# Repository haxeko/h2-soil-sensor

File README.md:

# H2 Soil Sensor — cảm biến độ ẩm đất Matter over Thread chạy pin

**Phiên bản 3:** bo mạch gọn **26 × 45 mm** chỉ gồm **ESP32-H2-WROOM-02C** + **tầng nguồn pin** (1 × CR123A, buck-boost
**TPS63900**, Iq 75 nA) + **một cổng J4 JST-PH 2.0 3P** cho module phổ biến **“Capacitive Soil Moisture Sensor v1.2”**
(module điện dung, ngõ ra analog AOUT). Pin hàn vào **2 pad J3** (“+” vuông, “−” tròn) bằng dây của hộp pin; nạp firmware qua
**8 pad tròn J1** (kẹp pogo 2.54 mm hoặc hàn dây) thay cho header. Thiết bị kết nối **Matter over Thread** như
**Sleepy End Device / ICD**; module chỉ được cấp nguồn (rail VSENS qua MOSFET) trong ~1.5 s mỗi lần đo.

| | |
|---|---|
|  | **Phần cứng**: KiCad (schematic phân cấp 5 sheet + PCB 2 lớp 26 × 45 mm, đã đi dây, DRC sạch), Gerber/BOM/CPL cho JLCPCB; linh kiện trên bo ≈ 2.1 USD (không gồm module ESP).<br><br>**Firmware**: ESP-IDF v6.0.2 + esp-matter (Matter 1.5): Soil Sensor (Soil Measurement), Humidity Sensor (bản sao độ ẩm đất, tương thích Apple/Google), Power Source (pin), ICD SIT/LIT, light-sleep, hiệu chuẩn bằng nút nhấn.<br><br>**Tuổi thọ pin ước tính** (đo mỗi 15 phút): ~2.2 năm (SIT, poll 15 s) – ~2.9 năm (LIT, poll 60 s); ~3.3 năm với LIT + đo mỗi 30 phút. |

## Tài liệu (tiếng Việt)

1. [Sơ đồ khối, lựa chọn linh kiện và module cảm biến](docs/01-so-do-khoi-va-linh-kien.md)
2. [Schematic chi tiết theo khối (nguồn, MCU, cổng cảm biến, nút/LED/pad nạp)](docs/02-schematic.md) — PDF: [`hardware/docs/schematic.pdf`](hardware/docs/schematic.pdf)
3. [BOM kèm mã LCSC (không gồm module ESP) và vật tư ngoài BOM](docs/03-bom.md)
4. [Hướng dẫn layout PCB](docs/04-layout-pcb.md)
5. [Dòng tiêu thụ từng trạng thái và tuổi thọ pin](docs/05-nang-luong-va-tuoi-tho-pin.md) — mô hình: [`docs/power_budget.py`](docs/power_budget.py)
6. [Cấu trúc project firmware và code chính](docs/06-firmware.md)
7. [Rủi ro và lưu ý khi dùng ngoài trời](docs/07-rui-ro-ngoai-troi.md)

## Cấu trúc repository

```
hardware/
├── h2-soil-sensor.kicad_pro / .kicad_sch / .kicad_pcb   # project KiCad (mở bằng KiCad ≥ 7)
├── power.kicad_sch, mcu.kicad_sch, sensors.kicad_sch, ui.kicad_sch
├── lib/h2soil.kicad_sym, lib/h2soil.pretty/             # symbol/footprint riêng (module ESP32-H2, pad nạp 2×4, WSON-10 via 0.3 mm)
├── fab/                                                 # Gerber+khoan (zip), BOM & CPL JLCPCB, danh sách không lắp máy
├── docs/                                                # schematic.pdf, pcb_top/bottom, assembly_top.pdf, render*.png, drc_report.txt
└── tools/                                               # script sinh schematic/PCB/fab từ design.py (+ router A*)
firmware/                                                # project ESP-IDF + esp-matter
docs/                                                    # tài liệu thiết kế
```

## Trạng thái kiểm chứng

| Hạng mục | Kết quả |
|---|---|
| Schematic | Netlist xuất bằng `kicad-cli` khớp 100 % với `design.py` (41 net, 43 ký hiệu = 39 linh kiện + 4 PWR_FLAG, mọi chân); PWR_FLAG đủ |
| PCB | 27/27 net tín hiệu đã đi dây (GND bằng đổ đồng 2 lớp); **DRC KiCad: 0 vi phạm, 0 pad chưa nối, 0 lỗi footprint** |
| Linh kiện | Mã LCSC kiểm tra tồn kho/giá qua API JLCPCB (11/2026) |
| Firmware | `idf.py build` thành công (ESP-IDF v6.0.2, esp-matter main / Matter 1.5, esp32h2), 1.66 MB, còn 16 % phân vùng OTA, không cảnh báo trong mã ứng dụng |
| Chưa làm được trong môi trường này | Chạy thử trên phần cứng thật, đo dòng thực tế, thử và hiệu chuẩn với module thật, kiểm tra anten/vỏ — cần bo mẫu |

## Bắt đầu nhanh

```bash
# Phần cứng: mở hardware/h2-soil-sensor.kicad_pro trong KiCad; file sản xuất ở hardware/fab/
# Firmware:
. esp-idf/export.sh && . esp-matter/export.sh
cd firmware && idf.py set-target esp32h2 && idf.py build
idf.py -p /dev/ttyACM0 flash monitor     # USB Serial/JTAG qua pad J1 (D+ = 8, D− = 7, GND = 2), pin đã lắp
```

1. Cáp đi kèm module thường là PH2.0 → đầu Dupont cái, **không cắm được vào J4**: dùng cáp PH2.0-3P hai đầu (nối thẳng) hoặc
   bấm lại đầu; đo để chắc GND → J4-1, VCC → J4-2, AOUT → J4-3.
2. Sau khi nạp: thiết bị mở BLE commissioning 15 phút — quét mã QR in trong log bằng ứng dụng Home (Apple Home, Google Home,
   SmartThings, Home Assistant…).
3. Hiệu chuẩn module: nhấn 2 lần nút khi đầu dò khô trong không khí (KHÔ), 3 lần khi đầu dò ngập nước tới vạch giới hạn (ƯỚT).

## Các phiên bản

| Phiên bản | Commit | Mô tả |
|---|---|---|
| v1 | `3c3f9e9` | Bo dạng que cắm đất 26 × 212 mm: đầu dò điện dung in trên PCB + TLC555, SHT40 và NTC trên bo, đế pin CR123A trên bo |
| v2 | `08ab9fe` | Bo 36 × 60 mm cắm module có sẵn: module đất, module I²C nhiệt/ẩm, đầu dò NTC; pin qua JST hoặc pad |
| v3 | hiện tại | Bo 26 × 45 mm chỉ cho module “Capacitive Soil Moisture Sensor v1.2”; pad nạp tròn thay header |

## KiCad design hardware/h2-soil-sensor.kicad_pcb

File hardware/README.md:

# Hardware (KiCad) – bo mạch v3, 26 × 45 mm

- Mở `h2-soil-sensor.kicad_pro` bằng KiCad 7/8/9. Thư viện riêng `h2soil` (symbol ESP32-H2-WROOM-02C, VBAT, VSENS; footprint
  module ESP32-H2, pad nạp `ProgPads_2x04_P2.54mm_D1.5mm` và WSON-10 via nhiệt 0.3 mm) đã khai báo trong `sym-lib-table` /
  `fp-lib-table` của project (`${KIPRJMOD}/lib/...`).
- `docs/schematic.pdf` – schematic 5 trang (sơ đồ khối, Power, MCU, Sensors, UI); `docs/pcb_top.*`, `docs/pcb_bottom.*`
  (mặt dưới nhìn gương), `docs/assembly_top.pdf` (vị trí + ký hiệu linh kiện); `docs/render.png`, `render_top.png`,
  `render_bottom.png` (ảnh minh hoạ); `docs/drc_report.txt` – báo cáo DRC (0 vi phạm, 0 pad chưa nối).
- `fab/h2-soil-sensor_gerbers.zip` (Gerber + khoan Excellon), `fab/h2-soil-sensor_BOM_JLCPCB.csv` và
  `fab/h2-soil-sensor_CPL_JLCPCB.csv` (35 linh kiện SMT lắp máy, kể cả U1), `fab/h2-soil-sensor_not_assembled.csv` (module ESP,
  J4 THT hàn tay, pad J1/J3).

## Cổng kết nối

| Ký hiệu | Loại | Chân |
|---|---|---|
| J3 | 2 pad xuyên lỗ hàn dây pin (lỗ 1.1 mm, bước 4.6 mm) | pad 1 vuông = “+” (VBAT_RAW), pad 2 tròn = “−” (GND); silkscreen “− BAT +” |
| J4 | JST-PH 2.0 3P (B3B-PH-K-S) – module độ ẩm đất | 1 = GND, 2 = VCC (VSENS), 3 = AOUT; J4 xoay 180°: chân 1 (GND) ở bên phải, nhãn silkscreen “A V G” |
| J1 | 8 pad tròn SMD Ø1.5 mm, lưới 2.54 mm, 2 hàng × 4, không phủ kem hàn | hàng sát mép bo (trái → phải): 1 = 3V3, 3 = TX, 5 = EN, 7 = D−; hàng trong: 2 = GND, 4 = RX, 6 = IO9, 8 = D+; pad 1 có chữ “1” |

Cáp đi kèm module thường là PH2.0 → Dupont cái, không vừa J4: dùng cáp PH2.0-3P hai đầu nối thẳng (hoặc bấm lại đầu) và đo
để chắc GND → GND trước khi cắm.

## Tái tạo từ script

Toàn bộ schematic/PCB được sinh từ `tools/design.py` (danh sách linh kiện, net, footprint, mã LCSC, ghi chú):

```bash
cd tools
python3 gen_footprints.py ..
python3 gen_schematic.py ..
python3 check_netlist.py ../h2-soil-sensor.kicad_sch    # "nets: 41  components checked: 43 ... OK"
python3 gen_pcb.py          # đặt linh kiện + đi dây (router.py) + đổ đồng + DRC; tự chạy với PYTHONHASHSEED=0 → kết quả lặp lại
python3 make_fab.py         # Gerber/khoan zip, BOM/CPL JLCPCB, not_assembled.csv, PDF, pcb_top/bottom.png
python3 render.py           # ảnh minh hoạ render_top/render_bottom/render.png
```

Yêu cầu: KiCad 7 (`kicad-cli`, module Python `pcbnew`), Python ≥ 3.10, numpy, Pillow, poppler-utils (render ảnh).
Các script giả định thư viện KiCad ở `/usr/share/kicad/{symbols,footprints}` (sửa hằng `KICAD_FP` / `KICAD_SYM_DIR` nếu khác).
Lưu ý: chạy lại `gen_pcb.py` sẽ ghi đè mọi chỉnh sửa tay trong `.kicad_pcb`.

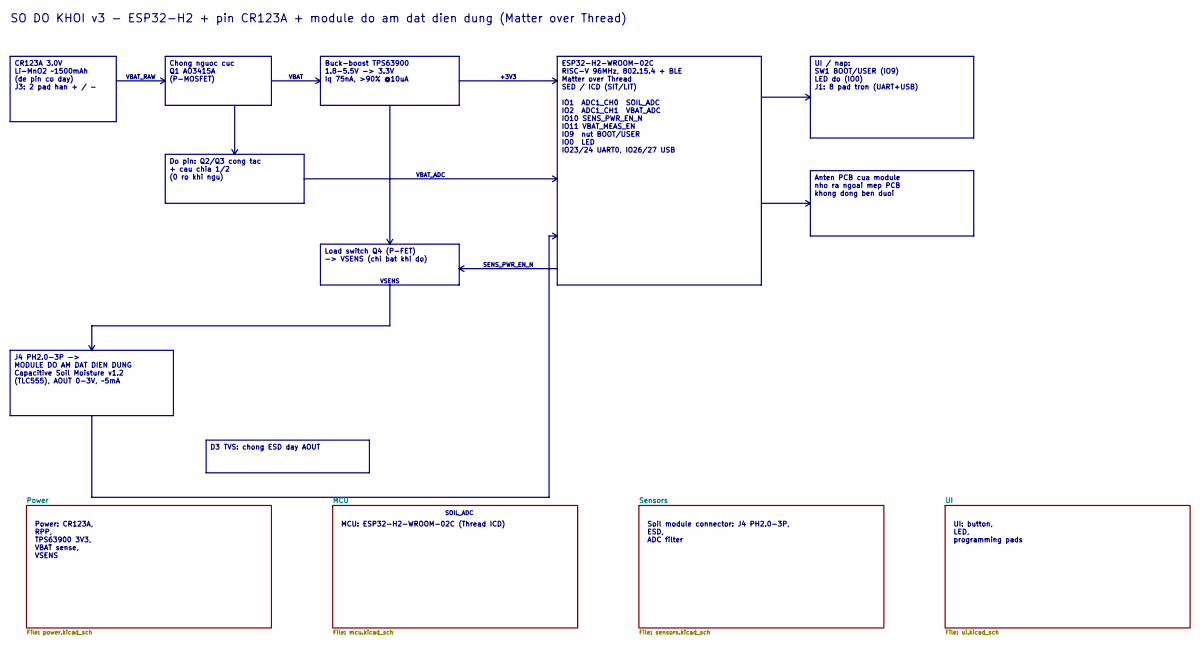
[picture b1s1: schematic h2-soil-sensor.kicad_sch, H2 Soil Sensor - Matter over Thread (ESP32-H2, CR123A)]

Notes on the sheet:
Power: CR123A, RPP, TPS63900 3V3, VBAT sense, VSENS
MCU: ESP32-H2-WROOM-02C (Thread ICD)
Soil module connector: J4 PH2.0-3P, ESD, ADC filter
UI: button, LED, programming pads
SO DO KHOI v3 - ESP32-H2 + pin CR123A + module do am dat dien dung (Matter over Thread)
CR123A 3.0V Li-MnO2 ~1500mAh (de pin co day) J3: 2 pad han + / -
Chong nguoc cuc Q1 AO3415A (P-MOSFET)
Buck-boost TPS63900 1.8-5.5V -> 3.3V Iq 75nA, >90% @10uA
ESP32-H2-WROOM-02C RISC-V 96MHz, 802.15.4 + BLE Matter over Thread SED / ICD (SIT/LIT) IO1 ADC1_CH0 SOIL_ADC IO2 ADC1_CH1 VBAT_ADC IO10 SENS_PWR_EN_N IO11 VBAT_MEAS_EN IO9 nut BOOT/USER IO0 LED IO23/24 UART0, IO26/27 USB
Do pin: Q2/Q3 cong tac + cau chia 1/2 (0 ro khi ngu)
Load switch Q4 (P-FET) -> VSENS (chi bat khi do)
J4 PH2.0-3P -> MODULE DO AM DAT DIEN DUNG Capacitive Soil Moisture v1.2 (TLC555), AOUT 0-3V, ~5mA
D3 TVS: chong ESD day AOUT
UI / nap: SW1 BOOT/USER (IO9) LED do (IO0) J1: 8 pad tron (UART+USB)
Anten PCB cua module nho ra ngoai mep PCB khong dong ben duoi
VBAT_RAW
VBAT
+3V3
VBAT_ADC
SENS_PWR_EN_N
VSENS
SOIL_ADC

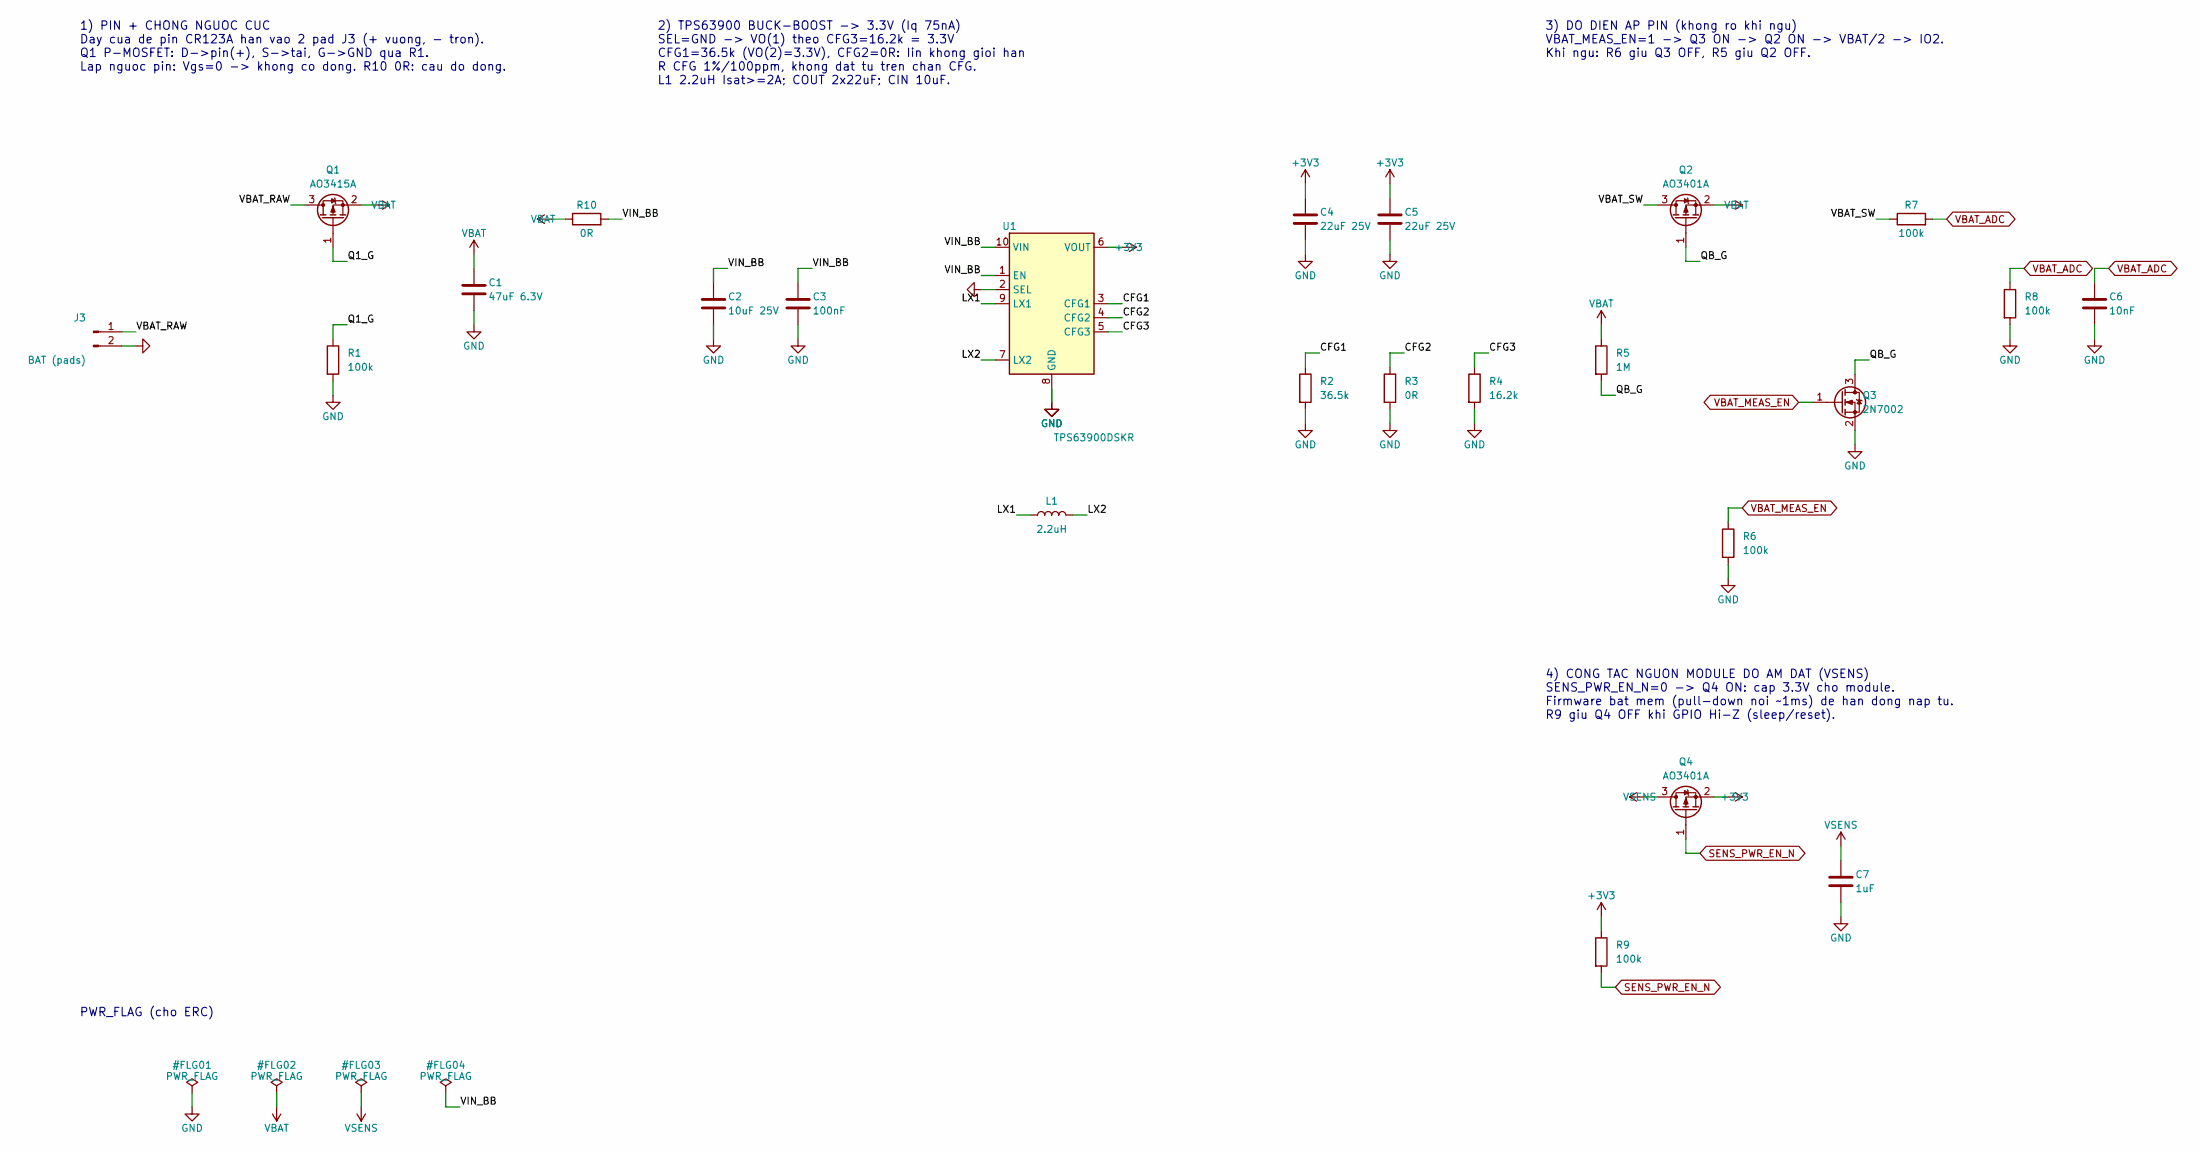
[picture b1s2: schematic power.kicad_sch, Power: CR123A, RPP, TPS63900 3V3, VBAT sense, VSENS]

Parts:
C1: 47uF 6.3V; C_0805_2012Metric; MPN CL21A476MQYNNNE; LCSC C16780
C2: 10uF 25V; C_0805_2012Metric; MPN CL21A106KAYNNNE; LCSC C15850
C3: 100nF; C_0603_1608Metric; MPN CC0603KRX7R9BB104; LCSC C14663
C4, C5: 22uF 25V; C_0805_2012Metric; MPN CL21A226MAQNNNE; LCSC C45783
C6: 10nF; C_0603_1608Metric; MPN CL10B103KB8NNNC; LCSC C1589
C7: 1uF; C_0603_1608Metric; MPN CL10A105KB8NNNC; LCSC C15849
J3: BAT (pads); SolderWire-0.5sqmm_1x02_P4.6mm_D0.9mm_OD2.1mm
L1: 2.2uH; L_1008_2520Metric; MPN TFM252012ALMA2R2MTAA; LCSC C404804
Q1: AO3415A; SOT-23; MPN AO3415A; LCSC C133233
Q2, Q4: AO3401A; SOT-23; MPN AO3401A; LCSC C15127
Q3: 2N7002; SOT-23; MPN 2N7002; LCSC C8545
R1, R6, R7, R8, R9: 100k; R_0603_1608Metric; MPN 0603WAF1003T5E; LCSC C25803
R2: 36.5k; R_0603_1608Metric; MPN 0603WAF3652T5E; LCSC C23029
R3, R10: 0R; R_0603_1608Metric; MPN 0603WAF0000T5E; LCSC C21189
R4: 16.2k; R_0603_1608Metric; MPN 0603WAF1622T5E; LCSC C22885
R5: 1M; R_0603_1608Metric; MPN 0603WAF1004T5E; LCSC C22935
U1: TPS63900DSKR; WSON-10-1EP_2.5x2.5mm_P0.5mm_EP1.2x2mm_ThermalVias_0.3mm; MPN TPS63900DSKR; LCSC C1518762

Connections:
+3V3: C4.1, C5.1, Q4.2 (S), R9.1, U1.6 (VOUT); also elsewhere on the board
CFG1: R2.1, U1.3 (CFG1)
CFG2: R3.1, U1.4 (CFG2)
CFG3: R4.1, U1.5 (CFG3)
GND: C1.2, C2.2, C3.2, C4.2, C5.2, C6.2, C7.2, J3.2, Q3.2 (S), R1.2, R2.2, R3.2, R4.2, R6.2, R8.2, U1.2 (SEL), U1.8 (GND), U1.11 (GND); also elsewhere on the board
LX1: L1.1, U1.9 (LX1)
LX2: L1.2, U1.7 (LX2)
Q1_G: Q1.1 (G), R1.1
QB_G: Q2.1 (G), Q3.3 (D), R5.2
SENS_PWR_EN_N: Q4.1 (G), R9.2; also elsewhere on the board
VBAT: C1.1, Q1.2 (S), Q2.2 (S), R5.1, R10.1
VBAT_ADC: C6.1, R7.2, R8.1; also elsewhere on the board
VBAT_MEAS_EN: Q3.1 (G), R6.1; also elsewhere on the board
VBAT_RAW: J3.1, Q1.3 (D)
VBAT_SW: Q2.3 (D), R7.1
VIN_BB: C2.1, C3.1, R10.2, U1.1 (EN), U1.10 (VIN)
VSENS: C7.1, Q4.3 (D); also elsewhere on the board

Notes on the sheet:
1) PIN + CHONG NGUOC CUC Day cua de pin CR123A han vao 2 pad J3 (+ vuong, - tron). Q1 P-MOSFET: D->pin(+), S->tai, G->GND qua R1. Lap nguoc pin: Vgs=0 -> khong co dong. R10 0R: cau do dong.
2) TPS63900 BUCK-BOOST -> 3.3V (Iq 75nA) SEL=GND -> VO(1) theo CFG3=16.2k = 3.3V CFG1=36.5k (VO(2)=3.3V), CFG2=0R: Iin khong gioi han R CFG 1%/100ppm, khong dat tu tren chan CFG. L1 2.2uH Isat>=2A; COUT 2x22uF; CIN 10uF.
3) DO DIEN AP PIN (khong ro khi ngu) VBAT_MEAS_EN=1 -> Q3 ON -> Q2 ON -> VBAT/2 -> IO2. Khi ngu: R6 giu Q3 OFF, R5 giu Q2 OFF.
4) CONG TAC NGUON MODULE DO AM DAT (VSENS) SENS_PWR_EN_N=0 -> Q4 ON: cap 3.3V cho module. Firmware bat mem (pull-down noi ~1ms) de han dong nap tu. R9 giu Q4 OFF khi GPIO Hi-Z (sleep/reset).
PWR_FLAG (cho ERC)

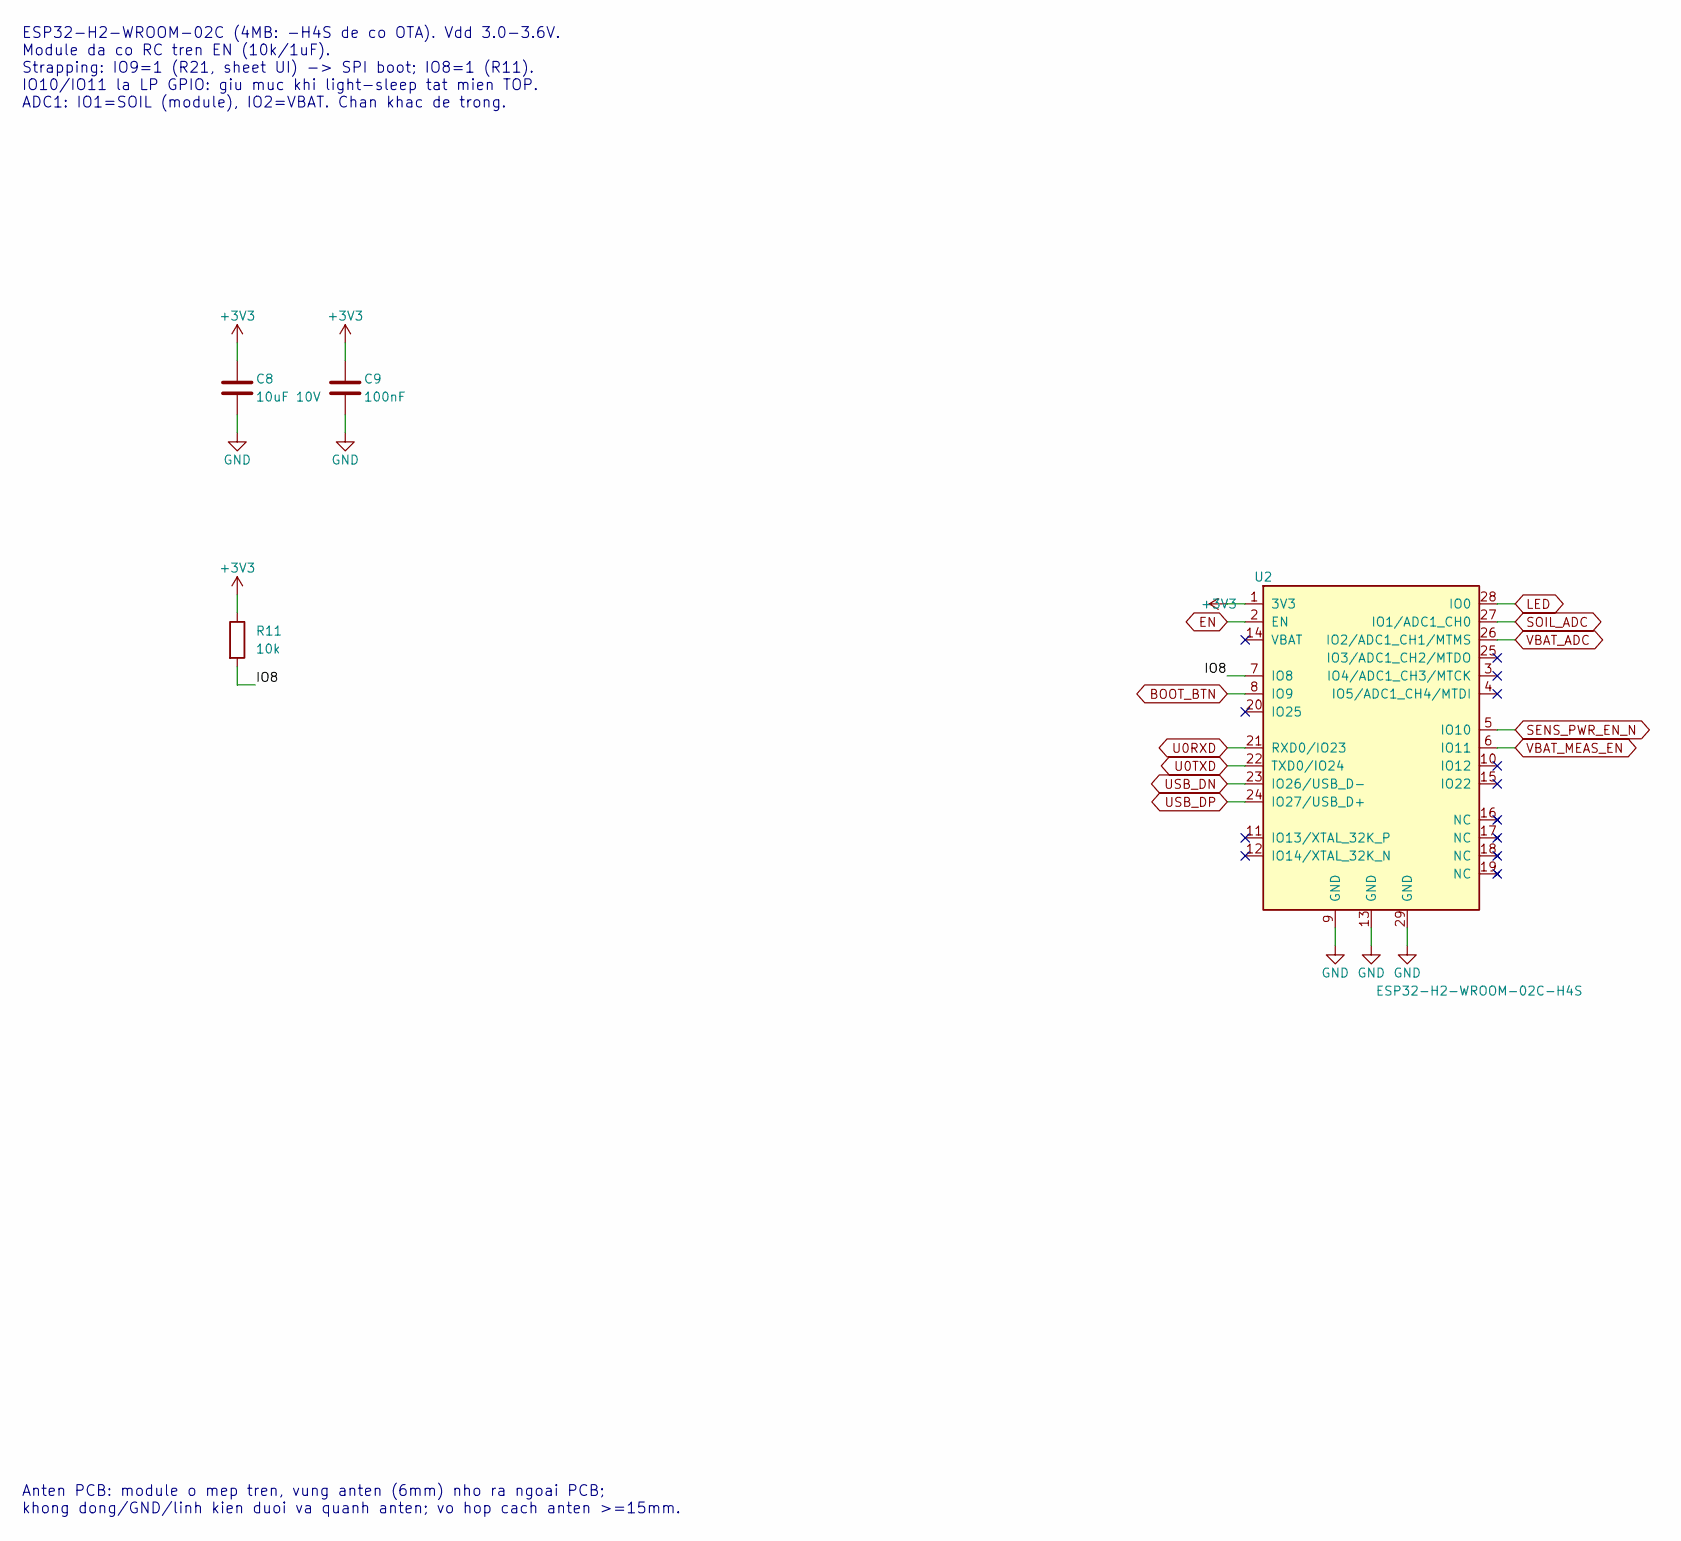
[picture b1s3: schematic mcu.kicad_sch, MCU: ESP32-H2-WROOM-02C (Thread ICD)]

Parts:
C8: 10uF 10V; C_0603_1608Metric; MPN CL10A106KP8NNNC; LCSC C19702
C9: 100nF; C_0603_1608Metric; MPN CC0603KRX7R9BB104; LCSC C14663
R11: 10k; R_0603_1608Metric; MPN 0603WAF1002T5E; LCSC C25804
U2: ESP32-H2-WROOM-02C-H4S; ESP32-H2-WROOM-02C; MPN ESP32-H2-WROOM-02C-H4S

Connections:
+3V3: C8.1, C9.1, R11.1, U2.1 (3V3); also elsewhere on the board
BOOT_BTN: U2.8 (IO9); also elsewhere on the board
EN: U2.2 (EN); also elsewhere on the board
GND: C8.2, C9.2, U2.9 (GND), U2.13 (GND), U2.29 (GND); also elsewhere on the board
IO8: R11.2, U2.7 (IO8)
LED: U2.28 (IO0); also elsewhere on the board
SENS_PWR_EN_N: U2.5 (IO10); also elsewhere on the board
SOIL_ADC: U2.27 (IO1/ADC1_CH0); also elsewhere on the board
U0RXD: U2.21 (RXD0/IO23); also elsewhere on the board
U0TXD: U2.22 (TXD0/IO24); also elsewhere on the board
USB_DN: U2.23 (IO26/USB_D-); also elsewhere on the board
USB_DP: U2.24 (IO27/USB_D+); also elsewhere on the board
VBAT_ADC: U2.26 (IO2/ADC1_CH1/MTMS); also elsewhere on the board
VBAT_MEAS_EN: U2.6 (IO11); also elsewhere on the board

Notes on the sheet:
ESP32-H2-WROOM-02C (4MB: -H4S de co OTA). Vdd 3.0-3.6V. Module da co RC tren EN (10k/1uF). Strapping: IO9=1 (R21, sheet UI) -> SPI boot; IO8=1 (R11). IO10/IO11 la LP GPIO: giu muc khi light-sleep tat mien TOP. ADC1: IO1=SOIL (module), IO2=VBAT. Chan khac de trong.
Anten PCB: module o mep tren, vung anten (6mm) nho ra ngoai PCB; khong dong/GND/linh kien duoi va quanh anten; vo hop cach anten >=15mm.

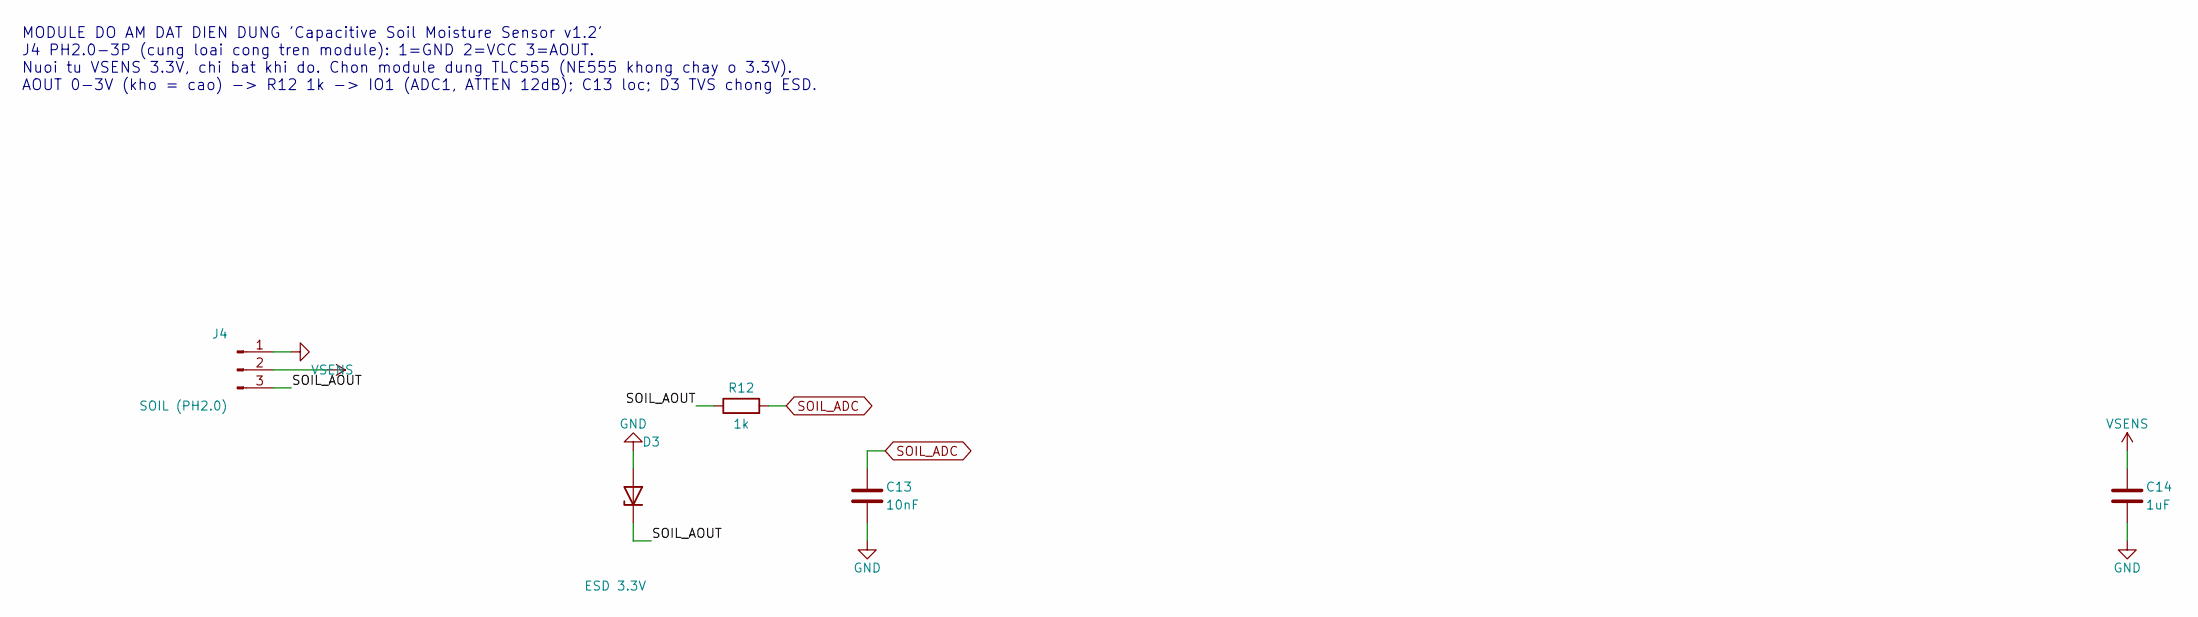
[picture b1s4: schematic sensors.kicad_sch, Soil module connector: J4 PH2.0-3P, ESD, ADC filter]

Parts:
C13: 10nF; C_0603_1608Metric; MPN CL10B103KB8NNNC; LCSC C1589
C14: 1uF; C_0603_1608Metric; MPN CL10A105KB8NNNC; LCSC C15849
D3: ESD 3.3V; D_SOD-523; MPN LESD5Z3.3T1G; LCSC C136161
J4: SOIL (PH2.0); JST_PH_B3B-PH-K_1x03_P2.00mm_Vertical; MPN B3B-PH-K-S(LF)(SN); LCSC C131339
R12: 1k; R_0603_1608Metric; MPN 0603WAF1001T5E; LCSC C21190

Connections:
GND: C13.2, C14.2, D3.2 (A), J4.1; also elsewhere on the board
SOIL_ADC: C13.1, R12.2; also elsewhere on the board
SOIL_AOUT: D3.1 (K), J4.3, R12.1
VSENS: C14.1, J4.2; also elsewhere on the board

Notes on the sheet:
MODULE DO AM DAT DIEN DUNG 'Capacitive Soil Moisture Sensor v1.2' J4 PH2.0-3P (cung loai cong tren module): 1=GND 2=VCC 3=AOUT. Nuoi tu VSENS 3.3V, chi bat khi do. Chon module dung TLC555 (NE555 khong chay o 3.3V). AOUT 0-3V (kho = cao) -> R12 1k -> IO1 (ADC1, ATTEN 12dB); C13 loc; D3 TVS chong ESD.

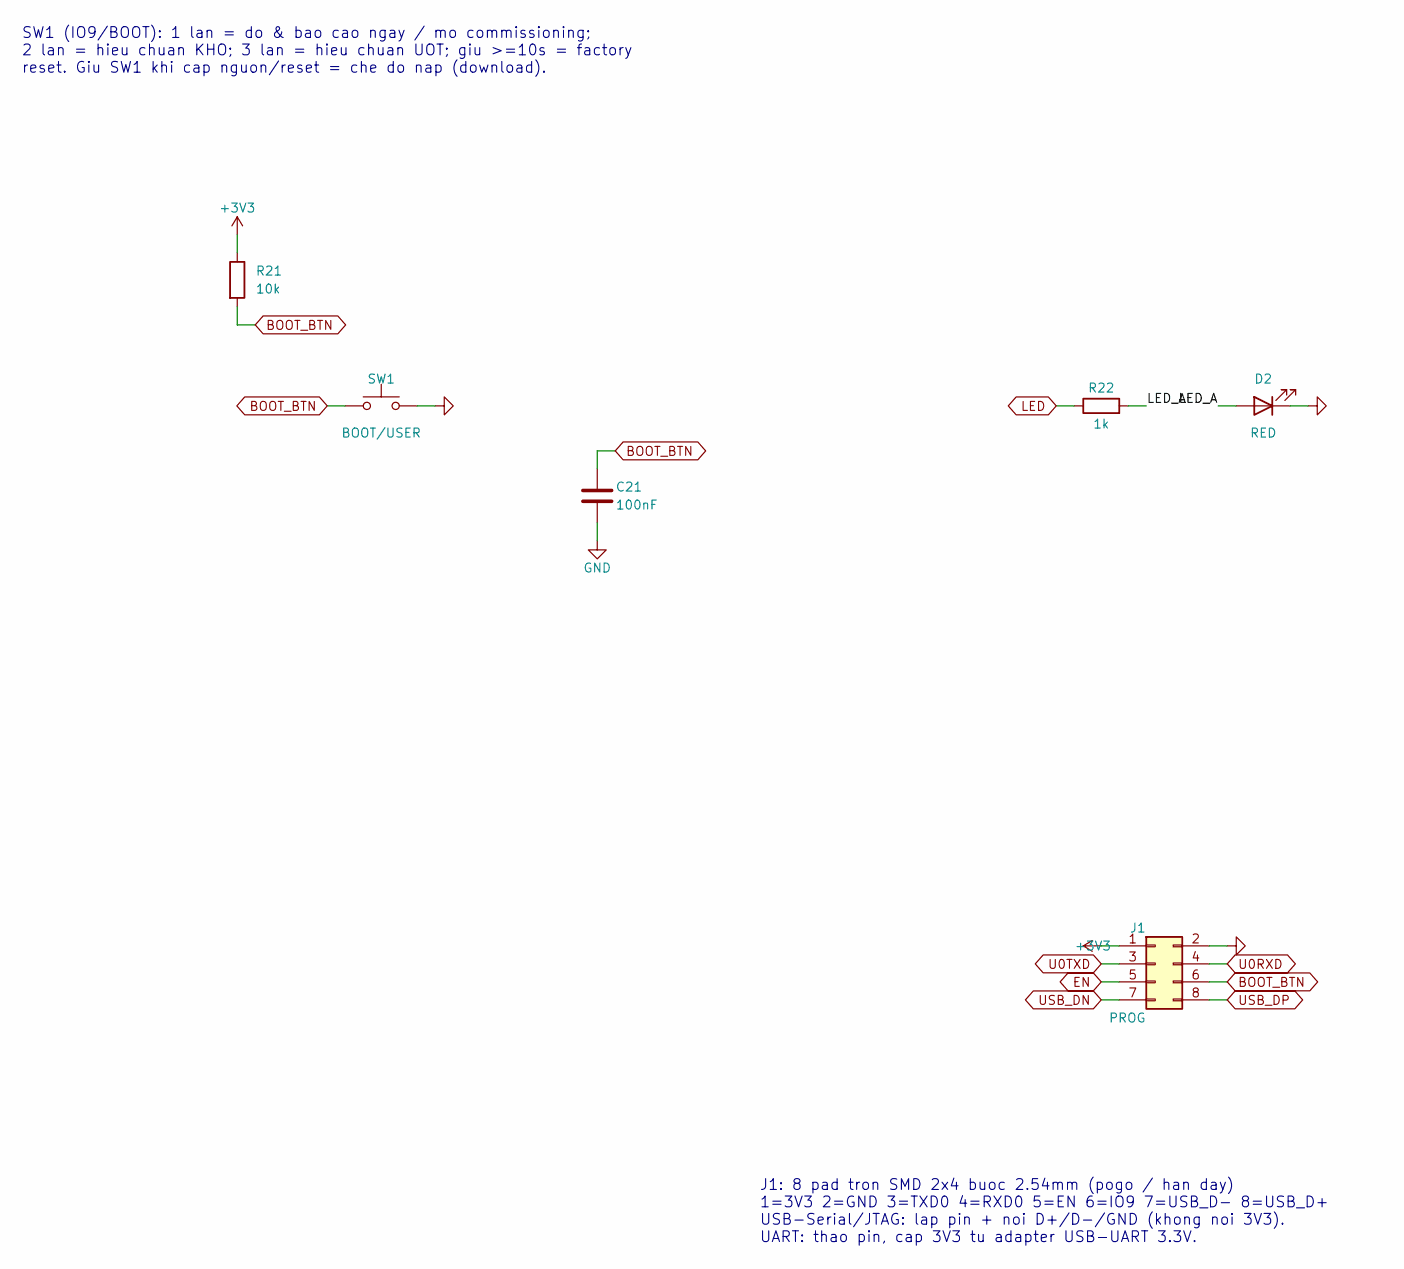
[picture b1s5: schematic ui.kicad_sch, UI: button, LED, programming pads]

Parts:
C21: 100nF; C_0603_1608Metric; MPN CC0603KRX7R9BB104; LCSC C14663
D2: RED; LED_0603_1608Metric; MPN KT-0603R; LCSC C2286
J1: PROG; ProgPads_2x04_P2.54mm_D1.5mm
R21: 10k; R_0603_1608Metric; MPN 0603WAF1002T5E; LCSC C25804
R22: 1k; R_0603_1608Metric; MPN 0603WAF1001T5E; LCSC C21190
SW1: BOOT/USER; SW_Push_1P1T_XKB_TS-1187A; MPN TS-1187A-B-A-B; LCSC C318884

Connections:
+3V3: J1.1, R21.1; also elsewhere on the board
BOOT_BTN: C21.1, J1.6, R21.2, SW1.1; also elsewhere on the board
EN: J1.5; also elsewhere on the board
GND: C21.2, D2.1 (K), J1.2, SW1.2; also elsewhere on the board
LED: R22.1; also elsewhere on the board
LED_A: D2.2 (A), R22.2
U0RXD: J1.4; also elsewhere on the board
U0TXD: J1.3; also elsewhere on the board
USB_DN: J1.7; also elsewhere on the board
USB_DP: J1.8; also elsewhere on the board

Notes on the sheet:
SW1 (IO9/BOOT): 1 lan = do & bao cao ngay / mo commissioning; 2 lan = hieu chuan KHO; 3 lan = hieu chuan UOT; giu >=10s = factory reset. Giu SW1 khi cap nguon/reset = che do nap (download).
J1: 8 pad tron SMD 2x4 buoc 2.54mm (pogo / han day) 1=3V3 2=GND 3=TXD0 4=RXD0 5=EN 6=IO9 7=USB_D- 8=USB_D+ USB-Serial/JTAG: lap pin + noi D+/D-/GND (khong noi 3V3). UART: thao pin, cap 3V3 tu adapter USB-UART 3.3V.

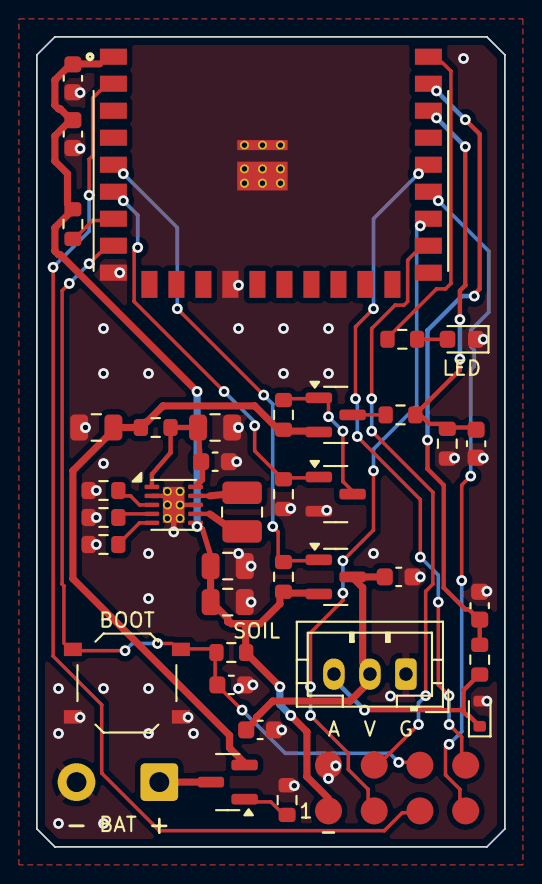
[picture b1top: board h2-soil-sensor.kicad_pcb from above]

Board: 2 copper layers, 26.0 x 45.0 mm, 39 parts (0 on the bottom side), 28 nets.

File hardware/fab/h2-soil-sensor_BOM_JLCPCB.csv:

Comment,Designator,Footprint,LCSC Part #,MPN,Manufacturer,Qty
47uF 6.3V,C1,C_0805_2012Metric,C16780,CL21A476MQYNNNE,Samsung,1
10uF 25V,C2,C_0805_2012Metric,C15850,CL21A106KAYNNNE,Samsung,1
100nF,"C3,C9,C21",C_0603_1608Metric,C14663,CC0603KRX7R9BB104,YAGEO,3
22uF 25V,"C4,C5",C_0805_2012Metric,C45783,CL21A226MAQNNNE,Samsung,2
10nF,"C6,C13",C_0603_1608Metric,C1589,CL10B103KB8NNNC,Samsung,2
1uF,"C7,C14",C_0603_1608Metric,C15849,CL10A105KB8NNNC,Samsung,2
10uF 10V,C8,C_0603_1608Metric,C19702,CL10A106KP8NNNC,Samsung,1
RED,D2,LED_0603_1608Metric,C2286,KT-0603R,Hubei KENTO,1
ESD 3.3V,D3,D_SOD-523,C136161,LESD5Z3.3T1G,LRC,1
2.2uH,L1,L_1008_2520Metric,C404804,TFM252012ALMA2R2MTAA,TDK,1
AO3415A,Q1,SOT-23,C133233,AO3415A,AOS,1
AO3401A,"Q2,Q4",SOT-23,C15127,AO3401A,AOS,2
2N7002,Q3,SOT-23,C8545,2N7002,CJ,1
100k,"R1,R6,R7,R8,R9",R_0603_1608Metric,C25803,0603WAF1003T5E,UNI-ROYAL,5
36.5k,R2,R_0603_1608Metric,C23029,0603WAF3652T5E,UNI-ROYAL,1
0R,"R3,R10",R_0603_1608Metric,C21189,0603WAF0000T5E,UNI-ROYAL,2
16.2k,R4,R_0603_1608Metric,C22885,0603WAF1622T5E,UNI-ROYAL,1
1M,R5,R_0603_1608Metric,C22935,0603WAF1004T5E,UNI-ROYAL,1
10k,"R11,R21",R_0603_1608Metric,C25804,0603WAF1002T5E,UNI-ROYAL,2
1k,"R12,R22",R_0603_1608Metric,C21190,0603WAF1001T5E,UNI-ROYAL,2
BOOT/USER,SW1,SW_Push_1P1T_XKB_TS-1187A,C318884,TS-1187A-B-A-B,XKB,1
TPS63900DSKR,U1,WSON-10-1EP_2.5x2.5mm_P0.5mm_EP1.2x2mm_ThermalVias_0.3mm,C1518762,TPS63900DSKR,Texas Instruments,1

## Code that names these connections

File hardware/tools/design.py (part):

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    # ===================================================================== POWER
    # --- battery terminals: two solder pads for the leads of the CR123A holder
    P(PW, "J3", "Connector", "Conn_01x02_Pin", "BAT (pads)", "Connector_Wire:SolderWire-0.5sqmm_1x02_P4.6mm_D0.9mm_OD2.1mm",
      "", "", "", 22.86, 83.82, 0, {"1": "VBAT_RAW", "2": "GND"}, note="2 pad han day pin (+ vuong / - tron)"),
    P(PW, "Q1", "Transistor_FET", "AO3401A", "AO3415A", SOT23, "C133233", "AO3415A", "AOS",
      66.04, 63.5, 90, {"1": "Q1_G", "2": "VBAT", "3": "VBAT_RAW"},
      note="P-MOSFET chong nguoc cuc, Vgs(th)<=1V, Rds(on) thap o Vgs=-1.8V"),
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
    # --- battery voltage measurement: high-side P-FET + N-FET level shifter, zero leakage when off
    P(PW, "Q2", "Transistor_FET", "AO3401A", "AO3401A", SOT23, "C15127", "AO3401A", "AOS",
      309.88, 63.5, 90, {"1": "QB_G", "2": "VBAT", "3": "VBAT_SW"}, note="Cong tac cau chia pin"),
    R(PW, "R5", "1M", 294.64, 88.9, 0, "VBAT", "QB_G", note="Keo gate Q2 len nguon -> OFF mac dinh"),
    P(PW, "Q3", "Transistor_FET", "2N7002", "2N7002", SOT23, "C8545", "2N7002", "CJ",
      337.82, 96.52, 0, {"1": "VBAT_MEAS_EN", "2": "GND", "3": "QB_G"}, note="Dich muc 3.3V -> gate Q2"),
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      50.8, 76.2, 0, {"1": "GND", "2": "VSENS", "3": "SOIL_AOUT"},
      note="Module do am dat dien dung v1.2/v2.0 (3.3-5.5V, AOUT 0-3V). Kiem tra thu tu day!"),
    R(SE, "R12", "1k", 121.92, 81.28, 90, "SOIL_AOUT", "SOIL_ADC", note="Han dong ESD/qua ap vao chan ADC"),
    C(SE, "C13", "10nF", 139.7, 93.98, 0, "SOIL_ADC", "GND", note="Loc + nguon cho ADC sample"),
    C(SE, "C14", "1uF", 317.5, 93.98, 0, "VSENS", "GND", note="Dem VSENS (nho de han dong khoi dong, module co tu rieng)"),
    # --- ESD protection of the analog line that leaves the enclosure
    P(SE, "D3", "Device", "D_Zener", "ESD 3.3V", "Diode_SMD:D_SOD-523", "C136161", "LESD5Z3.3T1G", "LRC",
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    P(UI, "SW1", "Switch", "SW_Push", "BOOT/USER", "Button_Switch_SMD:SW_Push_1P1T_XKB_TS-1187A", "C318884",
      "TS-1187A-B-A-B", "XKB", 71.12, 81.28, 0, {"1": "BOOT_BTN", "2": "GND"},
      note="IO9: nhan=commissioning/do ngay, 2 lan=hieu chuan kho, 3 lan=uot, giu 10s=factory reset"),
    R(UI, "R21", "10k", 50.8, 63.5, 0, "+3V3", "BOOT_BTN", note="Keo len (strapping IO9 = 1 -> SPI boot)"),
    C(UI, "C21", "100nF", 101.6, 93.98, 0, "BOOT_BTN", "GND", note="Chong doi phim"),
    P(UI, "D2", "Device", "LED", "RED", "LED_SMD:LED_0603_1608Metric", "C2286", "KT-0603R", "Hubei KENTO",
      195.58, 81.28, 180, {"2": "LED_A", "1": "GND"}, note="LED trang thai (chi nhay khi can)"),
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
